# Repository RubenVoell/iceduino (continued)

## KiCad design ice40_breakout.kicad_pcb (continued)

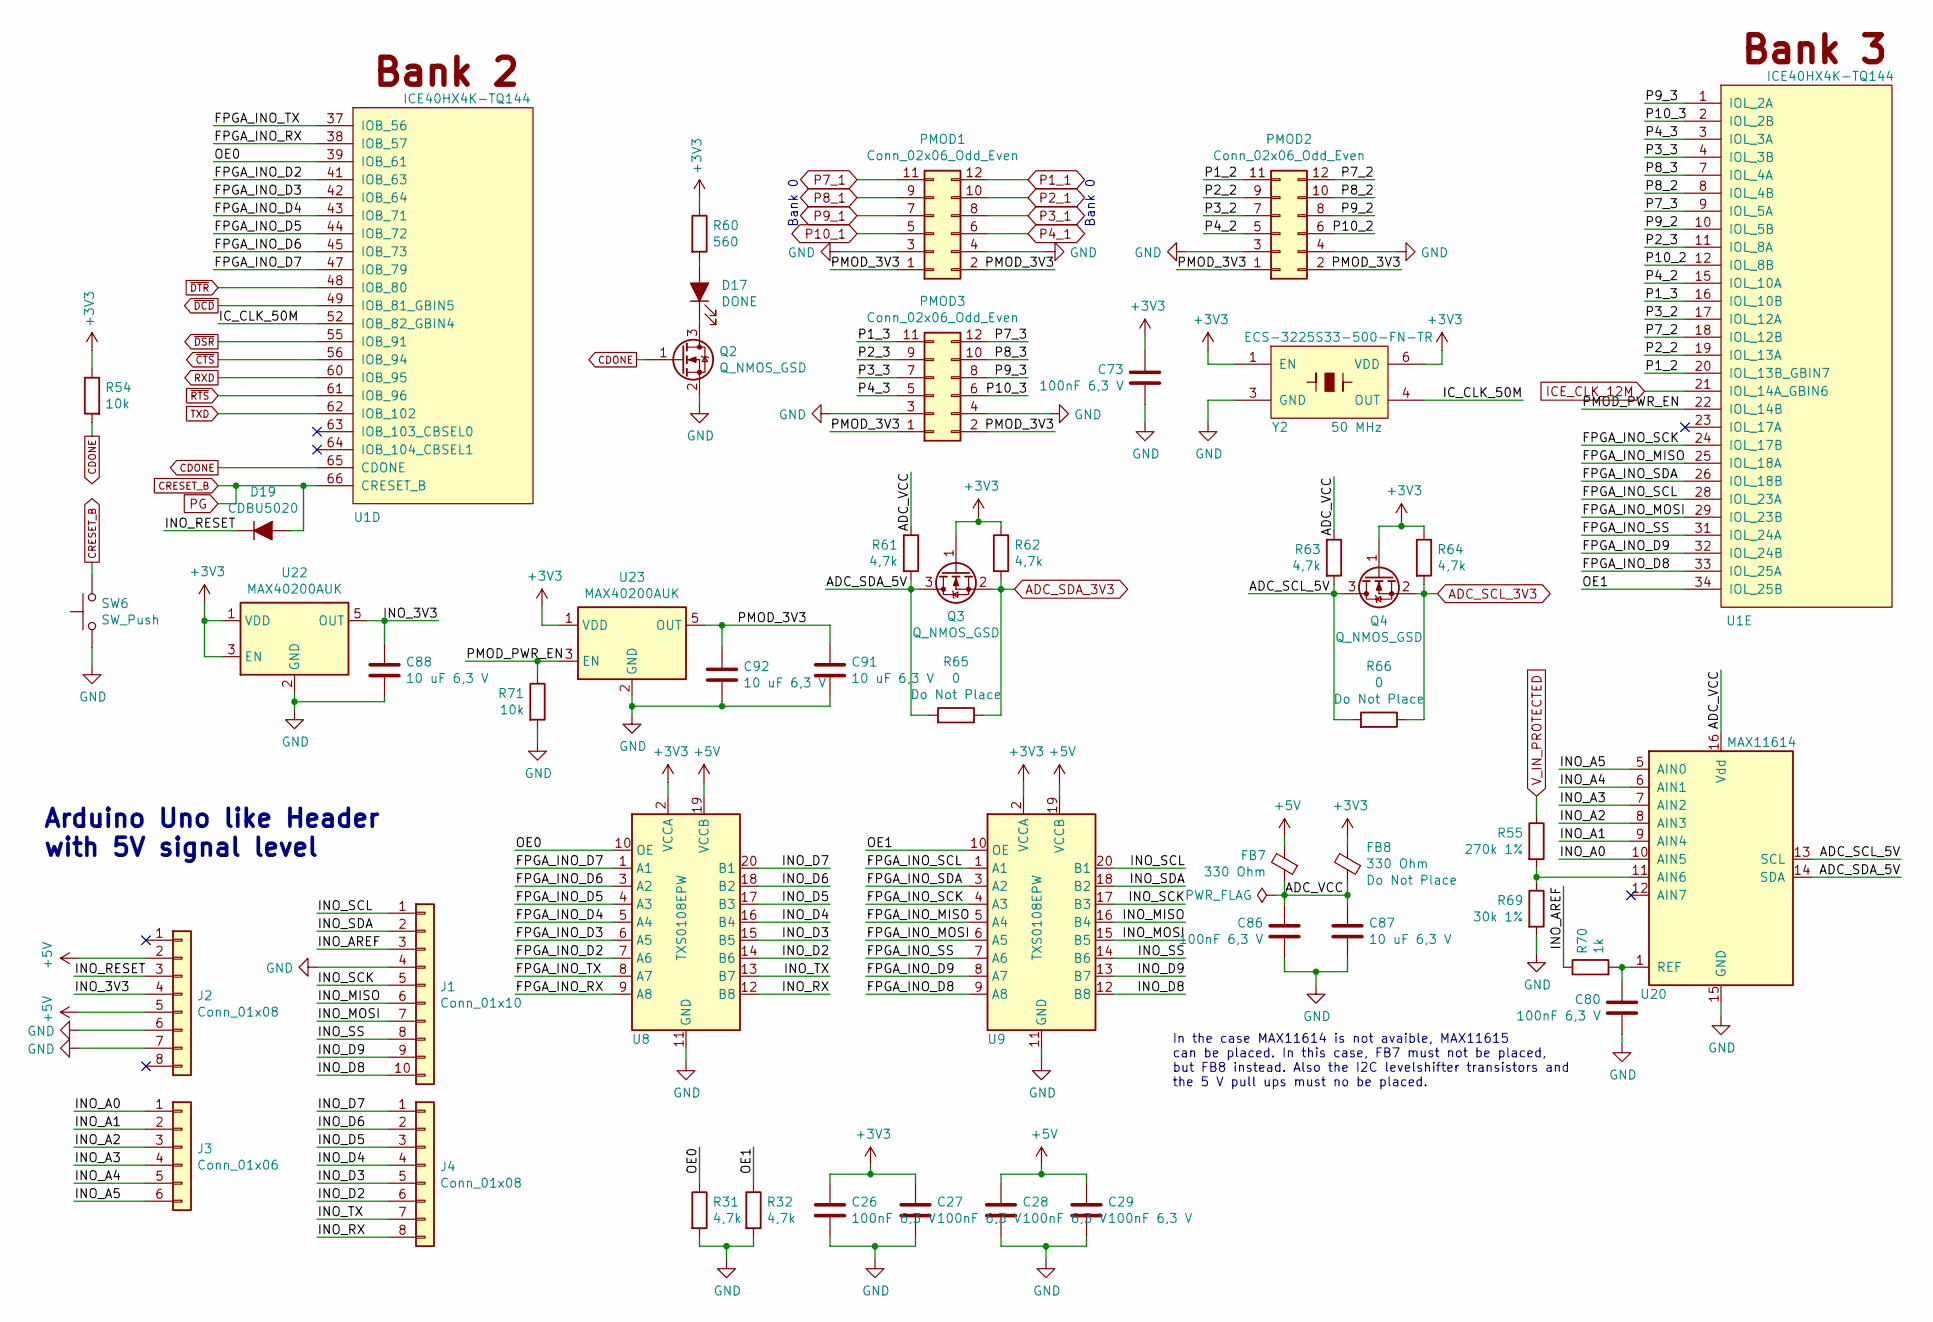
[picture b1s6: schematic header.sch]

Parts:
C26, C27, C28, C29, C73, C80, C86: 100nF 6,3 V; C_0603_1608Metric; Mfg Part Num CL10B104KB8NNNC; Digikey 1276-1000-1-ND
C87, C88, C91, C92: 10 uF 6,3 V; C_0603_1608Metric; Mfg Part Num CL10A106MQ8NNNC; Digikey 1276-1119-1-ND
D17: DONE; LED_0603_1608Metric
D19: CDBU5020; D_0603_1608Metric; Mfg Part Num CDBU0520; Digikey 641-1332-1-ND
FB7, FB8: 330 Ohm; R_0805_2012Metric; Mfg Part Num MPZ2012S331AT000; Digikey 445-1569-1-ND
J1: Conn_01x10; PinSocket_1x10_P2.54mm_Vertical
J2, J4: Conn_01x08; PinSocket_1x08_P2.54mm_Vertical
J3: Conn_01x06; PinSocket_1x06_P2.54mm_Vertical
PMOD1, PMOD2, PMOD3: Conn_02x06_Odd_Even; PinSocket_2x06_P2.54mm_Horizontal
Q2, Q3, Q4: Q_NMOS_GSD; SOT-23; Mfg Part Num DMN65D8L-7; Digikey DMN65D8L-7DICT-ND
R31, R32, R61, R62, R63, R64: 4,7k; R_0603_1608Metric
R54, R71: 10k; R_0603_1608Metric
R55: 270k 1%; R_0603_1608Metric
R60: 560; R_0603_1608Metric
R65, R66: 0; R_0603_1608Metric
R69: 30k 1%; R_0603_1608Metric
R70: 1k; R_0603_1608Metric
SW6: SW_Push; SW_SPST_TL3305A; Mfg Part Num TL3305AF160QG; Digikey EG5350CT-ND
U1: ICE40HX4K-TQ144; Mfg Part Num ICE40HX4K-TQ144; Digikey 220-1572-ND
U8, U9: TXS0108EPW; TSSOP-20_4.4x6.5mm_P0.65mm; Mfg Part Num TXS0108EPWR; Digikey 296-23011-1-ND
U20: MAX11614; QSOP-16_3.9x4.9mm_P0.635mm; Mfg Part Num MAX11614EEE+; Digikey MAX11614EEE+-ND
U22, U23: MAX40200AUK; SOT-23-5; Mfg Part Num MAX40200AUK+T; Digikey MAX40200AUK+TCT-ND
Y2: ECS-3225S33-500-FN-TR; Y_ECS-3225S_3.2x2.5mm_footprint; Mfg Part Num ECS-3225S33-500-FN-TR; Digikey XC2226CT-ND

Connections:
+3V3: C26.1, C27.1, C73.1, FB8.2, Q3.1 (G), Q4.1 (G), R54.1, R60.1, R62.1, R64.1, U8.2 (VCCA), U9.2 (VCCA), U22.1 (VDD), U22.3 (EN), U23.1 (VDD), Y2.1 (EN), Y2.6 (VDD); also elsewhere on the board
+5V: C28.1, C29.1, FB7.2, J2.2, J2.5, U8.19 (VCCB), U9.19 (VCCB); also elsewhere on the board
/Header/ADC_SCL_5V: Q4.3 (D), R63.2, R66.2, U20.13 (SCL)
/Header/ADC_SDA_5V: Q3.3 (D), R61.2, R65.2, U20.14 (SDA)
/Header/ADC_VCC: C86.1, C87.1, FB7.1, FB8.1, R61.1, R63.1, U20.16 (Vdd)
/Header/FPGA_INO_D2: U1.41 (IOB_63), U8.7 (A6)
/Header/FPGA_INO_D3: U1.42 (IOB_64), U8.6 (A5)
/Header/FPGA_INO_D4: U1.43 (IOB_71), U8.5 (A4)
/Header/FPGA_INO_D5: U1.44 (IOB_72), U8.4 (A3)
/Header/FPGA_INO_D6: U1.45 (IOB_73), U8.3 (A2)
/Header/FPGA_INO_D7: U1.47 (IOB_79), U8.1 (A1)
/Header/FPGA_INO_D8: U1.33 (IOL_25A), U9.9 (A8)
/Header/FPGA_INO_D9: U1.32 (IOL_24B), U9.8 (A7)
/Header/FPGA_INO_MISO: U1.25 (IOL_18A), U9.5 (A4)
/Header/FPGA_INO_MOSI: U1.29 (IOL_23B), U9.6 (A5)
/Header/FPGA_INO_RX: U1.38 (IOB_57), U8.9 (A8)
/Header/FPGA_INO_SCK: U1.24 (IOL_17B), U9.4 (A3)
/Header/FPGA_INO_SCL: U1.28 (IOL_23A), U9.1 (A1)
/Header/FPGA_INO_SDA: U1.26 (IOL_18B), U9.3 (A2)
/Header/FPGA_INO_SS: U1.31 (IOL_24A), U9.7 (A6)
/Header/FPGA_INO_TX: U1.37 (IOB_56), U8.8 (A7)
/Header/IC_CLK_50M: U1.52 (IOB_82_GBIN4), Y2.4 (OUT)
/Header/INO_3V3: C88.1, J2.4, U22.5 (OUT)
/Header/INO_A0: J3.1, U20.10 (AIN5)
/Header/INO_A1: J3.2, U20.9 (AIN4)
/Header/INO_A2: J3.3, U20.8 (AIN3)
/Header/INO_A3: J3.4, U20.7 (AIN2)
/Header/INO_A4: J3.5, U20.6 (AIN1)
/Header/INO_A5: J3.6, U20.5 (AIN0)
/Header/INO_AREF: J1.3, R70.1
/Header/INO_D2: J4.6, U8.14 (B6)
/Header/INO_D3: J4.5, U8.15 (B5)
/Header/INO_D4: J4.4, U8.16 (B4)
/Header/INO_D5: J4.3, U8.17 (B3)
/Header/INO_D6: J4.2, U8.18 (B2)
/Header/INO_D7: J4.1, U8.20 (B1)
/Header/INO_D8: J1.10, U9.12 (B8)
/Header/INO_D9: J1.9, U9.13 (B7)
/Header/INO_MISO: J1.6, U9.16 (B4)
/Header/INO_MOSI: J1.7, U9.15 (B5)
/Header/INO_RESET: D19.1 (K), J2.3
/Header/INO_RX: J4.8, U8.12 (B8)
/Header/INO_SCK: J1.5, U9.17 (B3)
/Header/INO_SCL: J1.1, U9.20 (B1)
/Header/INO_SDA: J1.2, U9.18 (B2)
/Header/INO_SS: J1.8, U9.14 (B6)
/Header/INO_TX: J4.7, U8.13 (B7)
/Header/OE0: R31.1, U1.39 (IOB_61), U8.10 (OE)
/Header/OE1: R32.1, U1.34 (IOL_25B), U9.10 (OE)
/Header/P1_2: PMOD2.11, U1.20 (IOL_13B_GBIN7)
/Header/P1_3: PMOD3.11, U1.16 (IOL_10B)
/Header/P2_2: PMOD2.9, U1.19 (IOL_13A)
/Header/P2_3: PMOD3.9, U1.11 (IOL_8A)
/Header/P3_2: PMOD2.7, U1.17 (IOL_12A)
/Header/P3_3: PMOD3.7, U1.4 (IOL_3B)
/Header/P4_2: PMOD2.5, U1.15 (IOL_10A)
/Header/P4_3: PMOD3.5, U1.3 (IOL_3A)
/Header/P7_2: PMOD2.12, U1.18 (IOL_12B)
/Header/P7_3: PMOD3.12, U1.9 (IOL_5A)
/Header/P8_2: PMOD2.10, U1.8 (IOL_4B)
/Header/P8_3: PMOD3.10, U1.7 (IOL_4A)
/Header/P9_2: PMOD2.8, U1.10 (IOL_5B)
/Header/P9_3: PMOD3.8, U1.1 (IOL_2A)
/Header/P10_2: PMOD2.6, U1.12 (IOL_8B)
/Header/P10_3: PMOD3.6, U1.2 (IOL_2B)
/Header/PMOD_3V3: C91.1, C92.1, PMOD1.1, PMOD1.2, PMOD2.1, PMOD2.2, PMOD3.1, PMOD3.2, U23.5 (OUT)
/Header/PMOD_PWR_EN: R71.1, U1.22 (IOL_14B), U23.3 (EN)
ADC_SCL_3V3: Q4.2 (S), R64.2, R66.1; also elsewhere on the board
ADC_SDA_3V3: Q3.2 (S), R62.2, R65.1; also elsewhere on the board
CDONE: Q2.1 (G), R54.2, U1.65 (CDONE); also elsewhere on the board
CRESET_B: D19.2 (A), SW6.2, U1.66 (CRESET_B); also elsewhere on the board
GND: C26.2, C27.2, C28.2, C29.2, C73.2, C80.2, C86.2, C87.2, C88.2, C91.2, C92.2, J1.4, J2.6, J2.7, PMOD1.3, PMOD1.4, PMOD2.3, PMOD2.4, PMOD3.3, PMOD3.4, Q2.2 (S), R31.2, R32.2, R69.2, R71.2, SW6.1, U8.11 (GND), U9.11 (GND), U20.15 (GND), U22.2 (GND), U23.2 (GND), Y2.3 (GND); also elsewhere on the board
ICE_CLK_12M: U1.21 (IOL_14A_GBIN6); also elsewhere on the board
unnamed: C80.1, R70.2, U20.1 (REF)
unnamed: D17.1 (K), Q2.3 (D)
unnamed: D17.2 (A), R60.2
unnamed: R55.2, R69.1, U20.11 (AIN6)
P1_1: PMOD1.12; also elsewhere on the board
P2_1: PMOD1.10; also elsewhere on the board
P3_1: PMOD1.8; also elsewhere on the board
P4_1: PMOD1.6; also elsewhere on the board
P7_1: PMOD1.11; also elsewhere on the board
P8_1: PMOD1.9; also elsewhere on the board
P9_1: PMOD1.7; also elsewhere on the board
P10_1: PMOD1.5; also elsewhere on the board
RXD: U1.60 (IOB_95); also elsewhere on the board
TXD: U1.62 (IOB_102); also elsewhere on the board
V_IN_PROTECTED: R55.1; also elsewhere on the board
~CTS~: U1.56 (IOB_94); also elsewhere on the board
~DCD~: U1.49 (IOB_81_GBIN5); also elsewhere on the board
~DSR~: U1.55 (IOB_91); also elsewhere on the board
~DTR~: U1.48 (IOB_80); also elsewhere on the board
~RTS~: U1.61 (IOB_96); also elsewhere on the board

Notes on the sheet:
Arduino Uno like Header with 5V signal level
Bank 0
In the case MAX11614 is not avaible, MAX11615 can be placed. In this case, FB7 must not be placed, but FB8 instead. Also the I2C levelshifter transistors and the 5 V pull ups must no be placed.

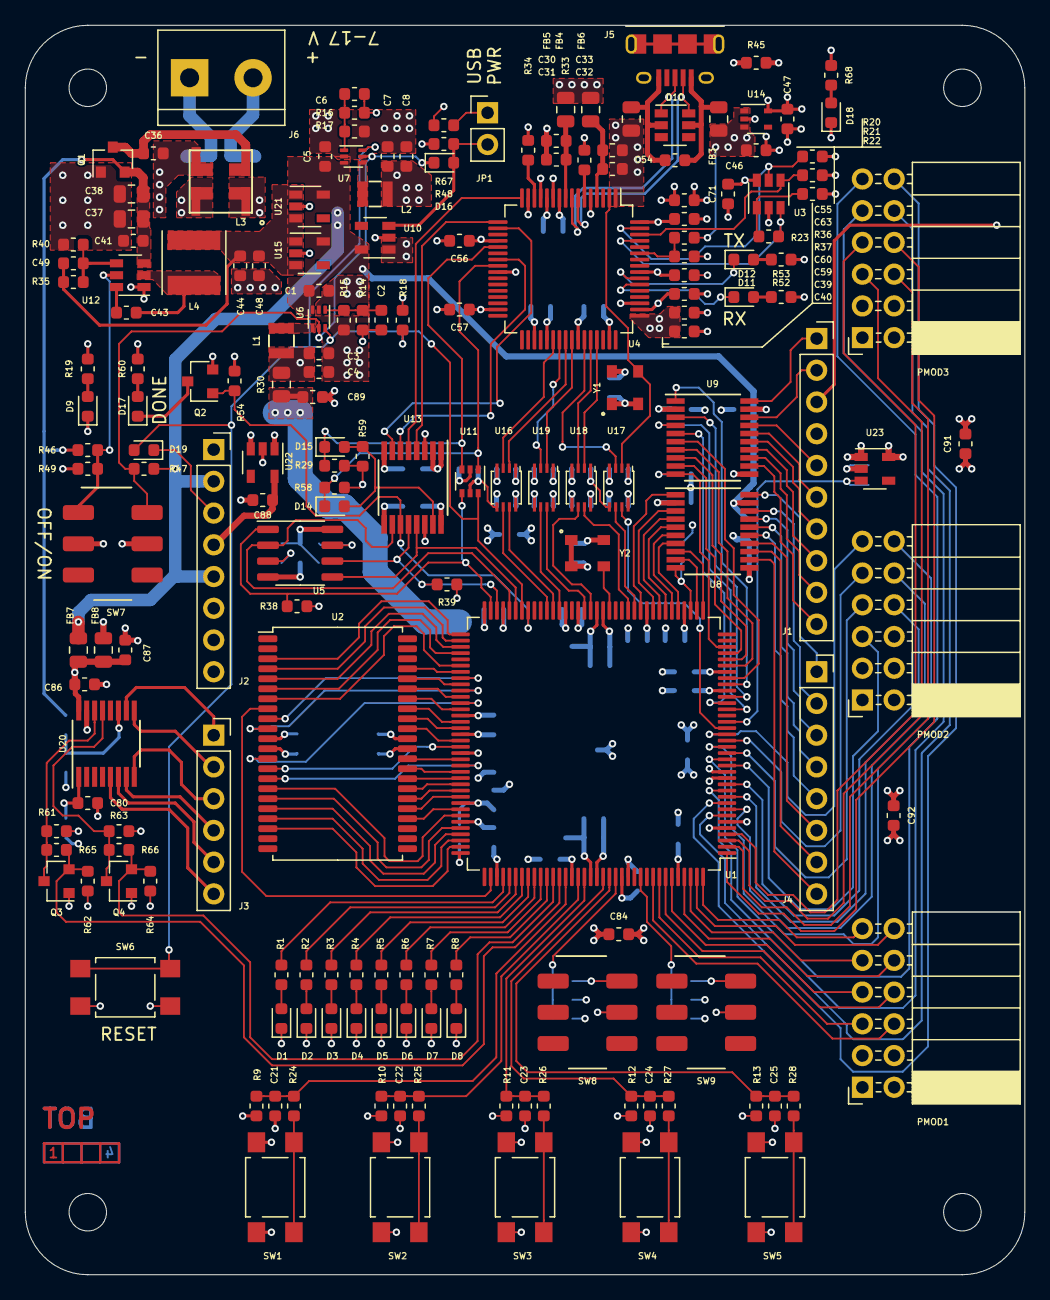
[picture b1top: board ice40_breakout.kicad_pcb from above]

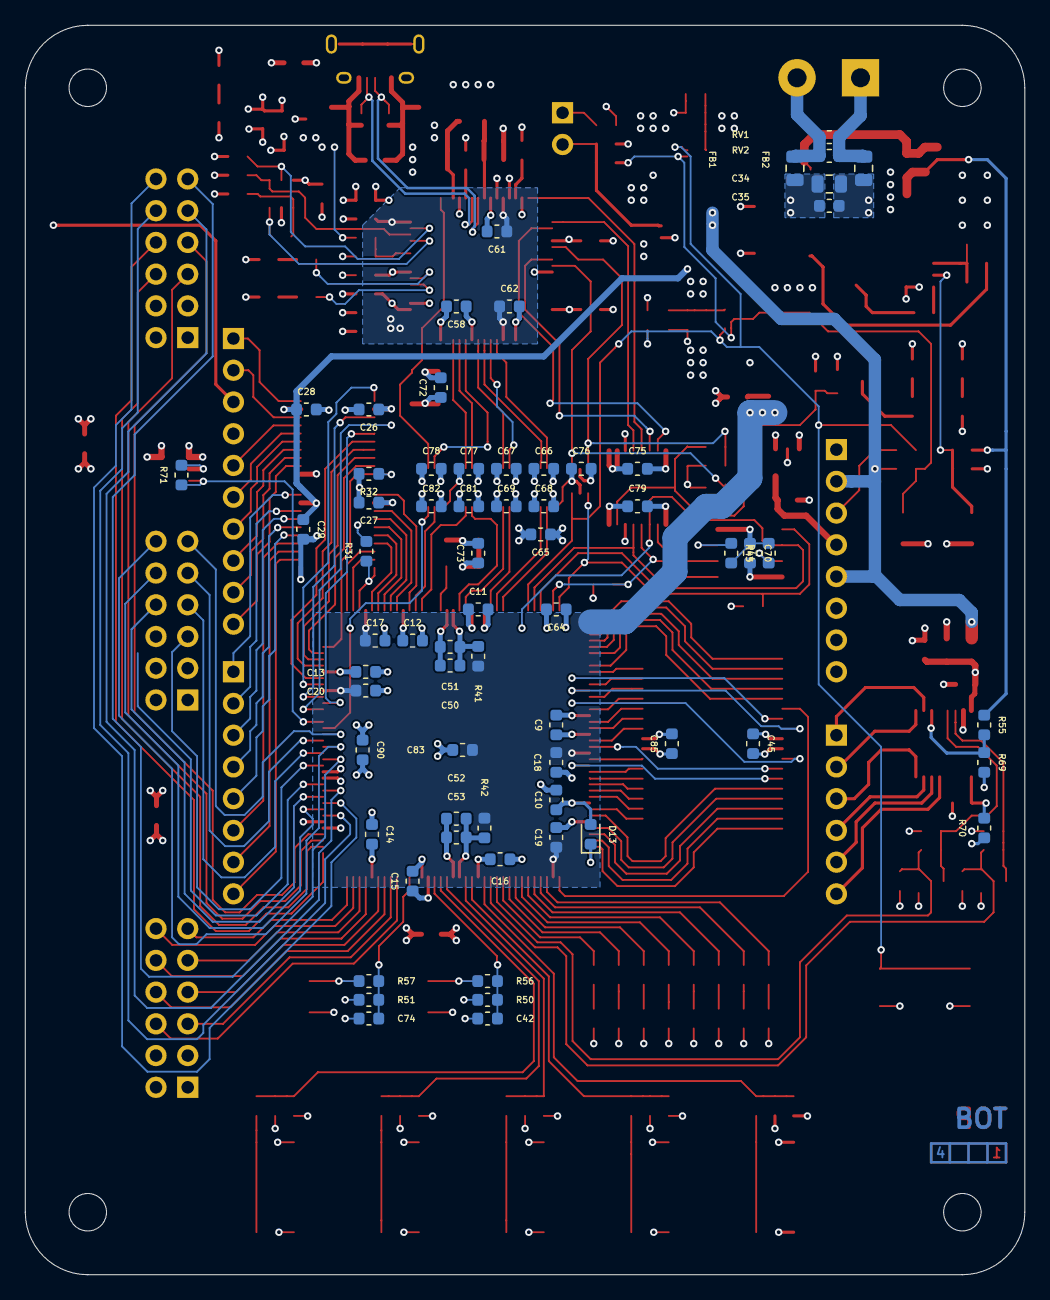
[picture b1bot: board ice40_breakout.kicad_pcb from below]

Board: 4 copper layers, 80.0 x 100.0 mm, 248 parts (66 on the bottom side), 222 nets.

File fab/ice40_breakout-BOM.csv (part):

Reference, Quantity, Value, Footprint, Datasheet, Description, Digikey, Mfg Name, Mfg Part Num, Spec, DNP, f
C1 C3 C5 C7 C8 C52 C50 C83 C4 C89 C84 C90 C40 C31 C33 C55 C54 C65 C87 C88 C92 C91 ,22,"10 uF 6,3 V","Capacitor_SMD:C_0603_1608Metric","~","CAP CER 10UF 6.3V X5R 0603","1276-1119-1-ND","Samsung Electro-Mechanics","CL10A106MQ8NNNC","Any","",""
C17 C18 C19 C20 C53 C51 C16 C15 C14 C13 C12 C11 C10 C9 C43 C21 C22 C23 C24 C25 C42 C74 C45 C85 C39 C30 C32 C66 C56 C57 C58 C59 C60 C64 C67 C68 C69 C71 C72 C70 C61 C62 C63 C77 C78 C75 C76 C81 C82 C79 C27 C28 C29 C26 C73 C86 C80 ,57,"100nF 6,3 V","Capacitor_SMD:C_0603_1608Metric","~","CAP CER 0.1UF 50V X7R 0603","1276-1000-1-ND","Samsung Electro-Mechanics","CL10B104KB8NNNC","Any","",""
C2 C6 C49 ,3,"10pF 6,3 V","Capacitor_SMD:C_0603_1608Metric","~","CAP CER 10PF 50V C0G/NP0 0603","1276-1027-1-ND","Samsung Electro-Mechanics","CL10C100JB8NNNC","Any","",""
C34 C37 C38 ,3,"10 uF 25 V","Capacitor_SMD:C_0805_2012Metric","~","CAP CER 10UF 25V X5R 0805","1276-2891-1-ND","Samsung Electro-Mechanics","CL21A106KAYNNNE","Any","",""
C35 C36 C41 ,3,"100nF 25 V","Capacitor_SMD:C_0603_1608Metric","~","CAP CER 0.1UF 50V X7R 0603","1276-1000-1-ND","Samsung Electro-Mechanics","CL10B104KB8NNNC","Any","",""
C47 C46 ,2,"1 uF 16 V","Capacitor_SMD:C_0603_1608Metric","~","CAP CER 1UF 16V X7R 0603","1276-6524-1-ND","Samsung Electro-Mechanics","CL10B105MO8NNWC","Any","",""
C48 C44 ,2,"22 uF 6,3 V","Capacitor_SMD:C_0603_1608Metric","~","CAP CER 22UF 6.3V X5R 0603","490-7611-1-ND","Murata Electronics North America","GRM188R60J226MEA0D","Any","",""
D10 ,1,"AOZ8904CIL","Package_TO_SOT_SMD:SOT-23-6","http://aosmd.com/res/data_sheets/AOZ8904CIL.pdf","TVS DIODE 5.5V 18V SOT23-6","785-1755-1-ND","Alpha & Omega Semiconductor Inc.","AOZ8904CIL","Spec","",""
D11 ,1,"RX LED","LED_SMD:LED_0603_1608Metric","~","LED RED DIFFUSED 1608 SMD","SML-D12U1WT86CT-ND","Rohm Semiconductor","SML-D12U1WT86","Any","",""
D12 ,1,"TX LED","LED_SMD:LED_0603_1608Metric","~","LED RED DIFFUSED 1608 SMD","SML-D12U1WT86CT-ND","Rohm Semiconductor","SML-D12U1WT86","Any","",""
D13 D16 D14 D15 D19 ,5,"CDBU5020","Diode_SMD:D_0603_1608Metric","http://www.comchiptech.com/admin/files/product/CDBU0520-HF-R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","DIODE SCHOTTKY 20V 500MA 0603","641-1332-1-ND","Comchip Technology","CDBU0520","Any","",""
D17 ,1,"DONE","LED_SMD:LED_0603_1608Metric","~","LED RED DIFFUSED 1608 SMD","SML-D12U1WT86CT-ND","Rohm Semiconductor","SML-D12U1WT86","Any","",""
D18 ,1,"USB ON LED","LED_SMD:LED_0603_1608Metric","~","LED RED DIFFUSED 1608 SMD","SML-D12U1WT86CT-ND","Rohm Semiconductor","SML-D12U1WT86","Any","",""
D9 D1 D2 D3 D4 D5 D6 D7 D8 ,9,"LED_ALT","LED_SMD:LED_0603_1608Metric","~","LED RED DIFFUSED 1608 SMD","SML-D12U1WT86CT-ND","Rohm Semiconductor","SML-D12U1WT86","Any","",""
FB1 FB2 FB4 FB5 FB3 FB6 FB7 FB8 ,8,"330 Ohm","Resistor_SMD:R_0805_2012Metric","https://product.tdk.com/info/en/catalog/datasheets/beads_com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","FERRITE BEAD 330 OHM 0805 1LN","445-1569-1-ND","TDK Corporation","MPZ2012S331AT000","Spec","",""
H1 H2 H3 H4 ,4,"MountingHole","MountingHole:MountingHole_3mm","~"
J1 ,1,"Conn_01x10","Connector_PinSocket_2.54mm:PinSocket_1x10_P2.54mm_Vertical","~","CONN HDR 10POS 0.1 GOLD PCB","732-2859-ND","Wurth Electronics Inc.","61301011821","Any","",""
J2 J4 ,2,"Conn_01x08","Connector_PinSocket_2.54mm:PinSocket_1x08_P2.54mm_Vertical","~","CONN HDR 8POS 0.1 GOLD PCB","S7041-ND","Sullins Connector Solutions","PPPC081LFBN-RC","Any","",""
J3 ,1,"Conn_01x06","Connector_PinSocket_2.54mm:PinSocket_1x06_P2.54mm_Vertical","~","CONN HDR 6POS 0.1 GOLD PCB","S7039-ND","Sullins Connector Solutions","PPPC061LFBN-RC","Any","",""
J5 ,1,"USB_B_Micro","footprints:Amphenol_microUSB_B_footprint","http://www.amphenol-icc.com/media/wysiwyg/files/drawing/1011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","CONN RCPT USB2.0 MICRO B SMD R/A","609-4618-1-ND","Amphenol ICC (FCI)","10118194-0001LF","Spec","",""
J6 ,1,"7-17 V IN","TerminalBlock:TerminalBlock_bornier-2_P5.08mm","https://www.cui.com/product/resource/digikeypdf/tb007-508.pdf","ERMINAL BLOCK, SCREW TYPE, 5.08","102-6203-ND","CUI Inc.","TB007-508-02BE","","",""
JP1 ,1,"VBUS_EN","Connector_PinHeader_2.54mm:PinHeader_1x02_P2.54mm_Vertical","~"
L1 L2 ,2,"1u","footprints:L_1008_2520Metric_2.5x2mm_footprint","https://www.yuden.co.jp/productdata/catalog/wound10_e.pdf","FIXED IND 1UH 2.7A 59 MOHM SMD","587-3225-1-ND","Taiyo Yuden","MAMK2520T1R0M","Spec","",""
L3 ,1,"L_DLW5BTM","footprints:L_Murata_DLW5BTM_5.00x5.00mm_footprint","https://www.murata.com/en-us/products/productdata/8796761587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","CMC 5A 2LN 250 OHM SMD","490-11111-1-ND","Murata Electronics North America","DLW5BTM251SQ2L","Spec","",""
L4 ,1,"4,7 uH","Inductor_SMD:L_Taiyo-Yuden_NR-50xx","~","FIXED IND 4.7UH 3.1A 37.7 MOHM","587-2373-1-ND","Taiyo Yuden","NR5040T4R7N","Spec","",""
PMOD2 PMOD3 PMOD1 ,3,"Conn_02x06_Odd_Even","Connector_PinSocket_2.54mm:PinSocket_2x06_P2.54mm_Horizontal","~","CONN HDR 12POS 0.1 GOLD PCB R/A ","S5559-ND","Sullins Connector Solutions","PPPC062LJBN-RC","Any","",""
Q1 ,1,"DMP3099L-7","Package_TO_SOT_SMD:SOT-23","https://www.diodes.com/assets/Datasheets/DMP3099L.pdf","MOSFET P-CH 30V SOT23","DMP3099L-7DICT-ND","Diodes Incorporated","DMP3099L-7","Spec","",""
Q2 Q4 Q3 ,3,"Q_NMOS_GSD","Package_TO_SOT_SMD:SOT-23","https://www.diodes.com/assets/Datasheets/DMN65D8L.pdf","MOSFET N-CH 60V 310MA SOT23","DMN65D8L-7DICT-ND","Diodes Incorporated","DMN65D8L-7","Spec","",""
R14 R15 ,2,"100k 1%","Resistor_SMD:R_0603_1608Metric","~","RES SMD 100K OHM 1% 1/10W 0603","311-100KHRCT-ND","Yageo","RC0603FR-07100KL","Any","",""
R16 ,1,"220k 1%","Resistor_SMD:R_0603_1608Metric","~","RES SMD 220K OHM 1% 1/10W 0603","311-220KHRCT-ND","Yageo","RC0603FR-07220KL","Any","",""
R17 ,1,"48,7k 1%","Resistor_SMD:R_0603_1608Metric","~","RES SMD 48.7K OHM 1% 1/10W 0603","311-48.7KHRCT-ND","Yageo","RC0603FR-0748K7L","Any","",""
R18 R47 R48 R67 R20 R21 R22 R43 R44 R38 R39 R37 R45 R59 R58 R29 R54 R71 ,18,"10k","Resistor_SMD:R_0603_1608Metric","~","RES 10K OHM 5% 1/10W 0603","RMCF0603JT10K0CT-ND","Stackpole Electronics Inc","RMCF0603JT10K0","Any","",""
R19 R1 R2 R3 R4 R5 R6 R7 R8 R52 R53 R68 R60 ,13,"560","Resistor_SMD:R_0603_1608Metric","~","RES 560 OHM 5% 1/8W 0603","2019-RK73B1JTTD561JCT-ND ","KOA Speer Electronics, Inc.","RK73B1JTTD561J ","Any","",""
R23 R34 ,2,"2,2k","Resistor_SMD:R_0603_1608Metric","~","RES SMD 2.2K OHM 1% 1/10W 0603","311-2.20KHRCT-ND","Yageo","RC0603FR-072K2L","Any","",""
R24 R25 R26 R27 R28 R56 R57 ,7,"470","Resistor_SMD:R_0603_1608Metric","~","RES 470 OHM 5% 1/10W 0603","RMCF0603JT470RCT-ND","Stackpole Electronics Inc","RMCF0603JT470R","Any","",""
R30 ,1,"0","Resistor_SMD:R_0805_2012Metric","~","RES SMD 0 OHM JUMPER 1/8W 0805","311-0.0ARCT-ND","Yageo","RC0805JR-070RL","Any","",""
R33 ,1,"12k","Resistor_SMD:R_0603_1608Metric","~","RES SMD 12K OHM 5% 1/10W 0603","311-12KGRCT-ND","Yageo","RC0603JR-0712KL","Any","",""
R35 ,1,"54k9 1%","Resistor_SMD:R_0603_1608Metric","~","RES SMD 54.9K OHM 1% 1/10W 0603","311-54.9KHRCT-ND","Yageo","RC0603FR-0754K9L","Any","",""
R36 ,1,"4k7","Resistor_SMD:R_0603_1608Metric","~","","","","","","DNP",""
R40 ,1,"10k 1%","Resistor_SMD:R_0603_1608Metric","~","RES SMD 10K OHM 1% 1/10W 0603","311-10.0KHRCT-ND","Yageo","RC0603FR-0710KL","Any","",""
R42 R41 ,2,"100","Resistor_SMD:R_0603_1608Metric","~","RES 100 OHM 1% 1/10W 0603","RMCF0603FT100RCT-ND","Stackpole Electronics Inc","RMCF0603FT100R","Any","",""
R46 ,1,"33k","Resistor_SMD:R_0603_1608Metric","~","RES SMD 33K OHM 5% 1/10W 0603","311-33KGRCT-ND","Yageo","RC0603JR-0733KL","Any","",""
R49 ,1,"22k","Resistor_SMD:R_0603_1608Metric","~","RES SMD 22K OHM 1% 1/10W 0603","311-22.0KHRCT-ND","Yageo","RC0603FR-0722KL","Any","",""
R55 ,1,"270k 1%","Resistor_SMD:R_0603_1608Metric","~","RES SMD 270K OHM 1% 1/10W 0603","311-270KHRCT-ND","Yageo","RC0603FR-07270KL","Any","",""
R65 R66 ,2,"0","Resistor_SMD:R_0603_1608Metric","~","","","","","","Do Not Place",""
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
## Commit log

2019-04-07 Made a first symbol for the ice40hx4k with TQFP144 footprint.
    Also added a FTDI chip for programming, two flashes and a SRAM to the schematic
2019-04-07 Add vim swap files to .gitignore
2019-04-07 Developed the ice40 symbol
2019-04-07 Made a symbol for the SRAM
2019-04-07 Made a overview on the toplevel schematic and added the SRAM subschematic.
2019-04-20 Footprint and 3d model for usb-micro
2019-04-20 Footprint for Taiyo Yuden 1008
2019-04-20 Foorptint and 3d model for tl3305a buttons
2019-04-20 Add symbol for aoz8904cil TVS Diode
2019-04-20 Add symbol for is61wv5128edbll sram
2019-04-20 Add symbol for TLV62568APDRLR step down converter
2019-04-20 sram, ui, power, flash and header
    SRAM: mostly done. Changed the choosen IC to a faster one in a differenc housing.
    POWER: added some step down converter for 3.3 V and 1.2 V. The 1.2 V is oversized and could be changed to a smaller one
    Programmer: added flash.
    HEADER: Added Arduino Uno like headers with 5 V signal level. Analog is not connected now, will get an I2C ADC in future. Also added 3 digilent pmod styled connector with 3.3 V signal level.
    UI: added 5 buttons and 8 LEDs. There is some space left over, maybe double the LED count in future.
2019-04-21 Symbol, Footprint and 3d model for ECS-3225S crystal oscillator
2019-04-21 Progress on FTDI - added Oscillator and 1.8 V supply
2019-04-22 ECS-3225S Symbol: remove not existing pads
2019-04-22 Continued on Programmer, moved the header signals around the package to free some space for a fully featured UART/RS232(TTL)
2019-05-05 Added switches, added 5 V rail and 17 V input(with filtering). Power is mostly done.
    Also added a first version of buffers to ftdi chip. I'll change the evtl.
    Started to route power section.
2019-05-06 Continued on Power PCB design
2019-05-07 Implemented proper Powerseparation between FTDI and FPGA. The old solution may not work correctly
2019-05-07 Continued on routing
2019-05-07 Continued on placing
2019-05-09 Continued with routing
2019-05-11 Continued with routing and added ADC
2019-05-12 Changed power isolation to usb power to use an open drain translator for the reset signals. Continued on routing
2019-05-12 Routing mostly done
2019-05-12 Added more BOM information, updated fpga symbol, added some more 3d models
2019-05-12 More BOM Information, more 3d Models
2019-05-12 Add rendering
2019-05-14 Corrected a few footprints
2019-05-15 Finished Silkscreen and added layer markings as specified by manufacturer
2019-05-16 Produktionsdaten
2019-05-17 Fixed rotated PMODs
2019-05-17 New production data2
2019-05-17 refreshed schematic pdf
2019-05-22 More complete BOM
2019-07-10 Add interactive BOM
2019-08-09 Add License
